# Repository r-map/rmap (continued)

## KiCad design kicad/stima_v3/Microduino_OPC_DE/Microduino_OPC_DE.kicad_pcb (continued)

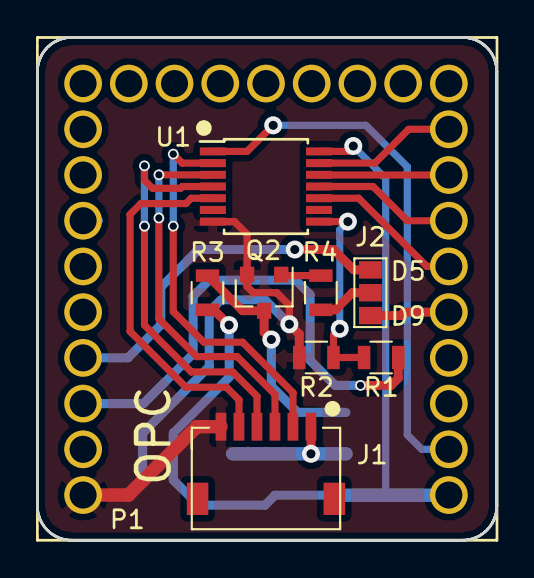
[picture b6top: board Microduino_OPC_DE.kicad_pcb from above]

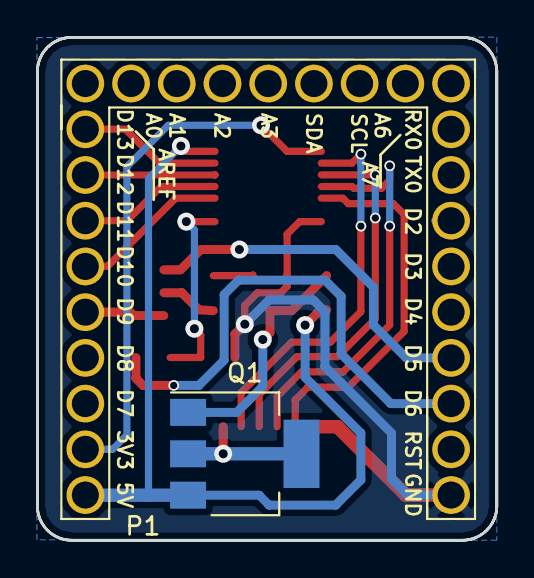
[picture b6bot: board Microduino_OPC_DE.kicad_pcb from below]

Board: 2 copper layers, 25.5 x 27.9 mm, 10 parts (2 on the bottom side), 19 nets.

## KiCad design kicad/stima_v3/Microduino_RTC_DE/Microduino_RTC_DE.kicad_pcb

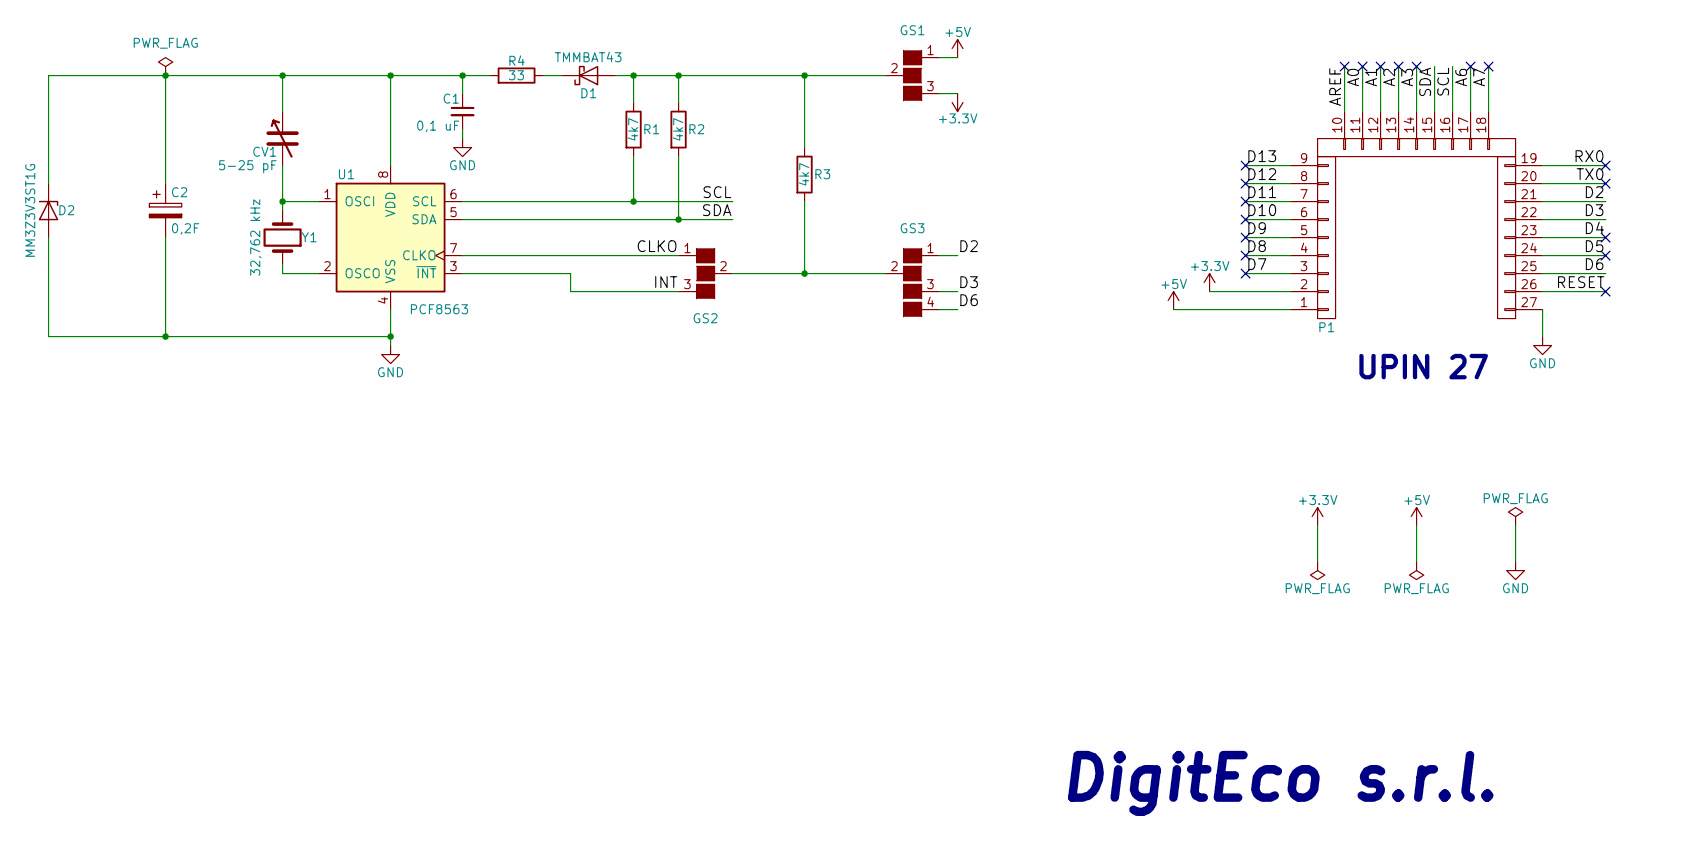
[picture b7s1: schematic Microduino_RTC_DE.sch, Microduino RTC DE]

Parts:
C1: 0,1 uF; C_0805
C2: 0,2F; Supercap
CV1: 5-25 pF; C_1206
D1: TMMBAT43; D_MiniMELF_Standard
D2: MM3Z3V3ST1G; D_SOD-323
GS1, GS2: GS3
GS3: GS4
P1: CONN_1x27; Upin_27
R1, R2, R3: 4k7; R_0805
R4: 33; R_0805
U1: PCF8563; SOIC-8_3.9x4.9mm_Pitch1.27mm
Y1: 32,762 kHz; Crystal_SMD_G8-2pin_3.2x1.5mm_HandSoldering

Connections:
+3V3: GS1.3 (G3), P1.2
+5V: GS1.1 (G1), P1.1
/A0: P1.11
/A1: P1.12
/A2: P1.13
/A3: P1.14
/A6: P1.17
/A7: P1.18
/AREF: P1.10
/CLKO: GS2.1 (G1), U1.7 (CLKO); also elsewhere on the board
/D2: GS3.1 (G1), P1.21
/D3: GS3.3 (G3), P1.22
/D4: P1.23
/D5: P1.24
/D6: GS3.4 (G4), P1.25
/D7: P1.3
/D8: P1.4
/D9: P1.5
/D10: P1.6
/D11: P1.7
/D12: P1.8
/D13: P1.9
/INT: GS2.3 (G3), U1.3 (~INT~); also elsewhere on the board
/RESET: P1.26
/RX0: P1.19
/SCL: P1.16, R1.2, U1.6 (SCL)
/SDA: P1.15, R2.2, U1.5 (SDA)
/TX0: P1.20
GND: C1.2, C2.2, D2.2 (A), P1.27, U1.4 (VSS)
unnamed: C1.1, C2.1, CV1.1, D2.1 (K), R4.2, U1.8 (VDD)
unnamed: CV1.2, U1.1 (OSCI), Y1.2
unnamed: D1.1 (K), R4.1
unnamed: D1.2 (A), GS1.2 (G2), R1.1, R2.1, R3.1
unnamed 33: GS2.2 (G2), GS3.2 (G2), R3.2; also elsewhere on the board
unnamed: U1.2 (OSCO), Y1.1

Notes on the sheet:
UPIN 27
DigitEco s.r.l.

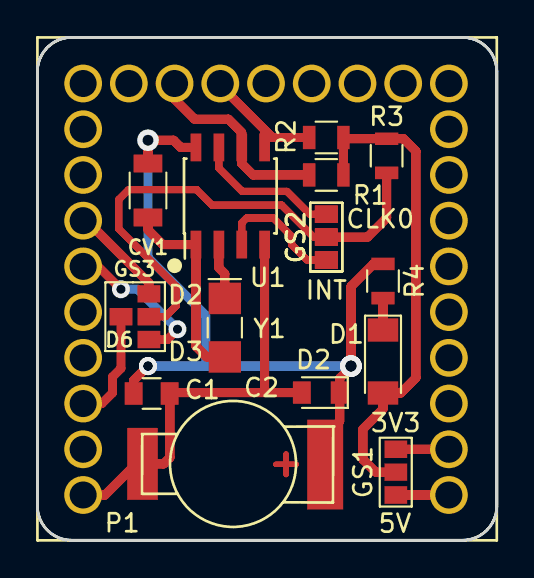
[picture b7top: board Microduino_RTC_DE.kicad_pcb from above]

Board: 2 copper layers, 25.5 x 27.9 mm, 16 parts (1 on the bottom side), 16 nets.

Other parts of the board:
GS2#2: GS3

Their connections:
/CLKO: GS2#2.1; also elsewhere on the board
/INT: GS2#2.3; also elsewhere on the board
unnamed 33: GS2#2.2; also elsewhere on the board

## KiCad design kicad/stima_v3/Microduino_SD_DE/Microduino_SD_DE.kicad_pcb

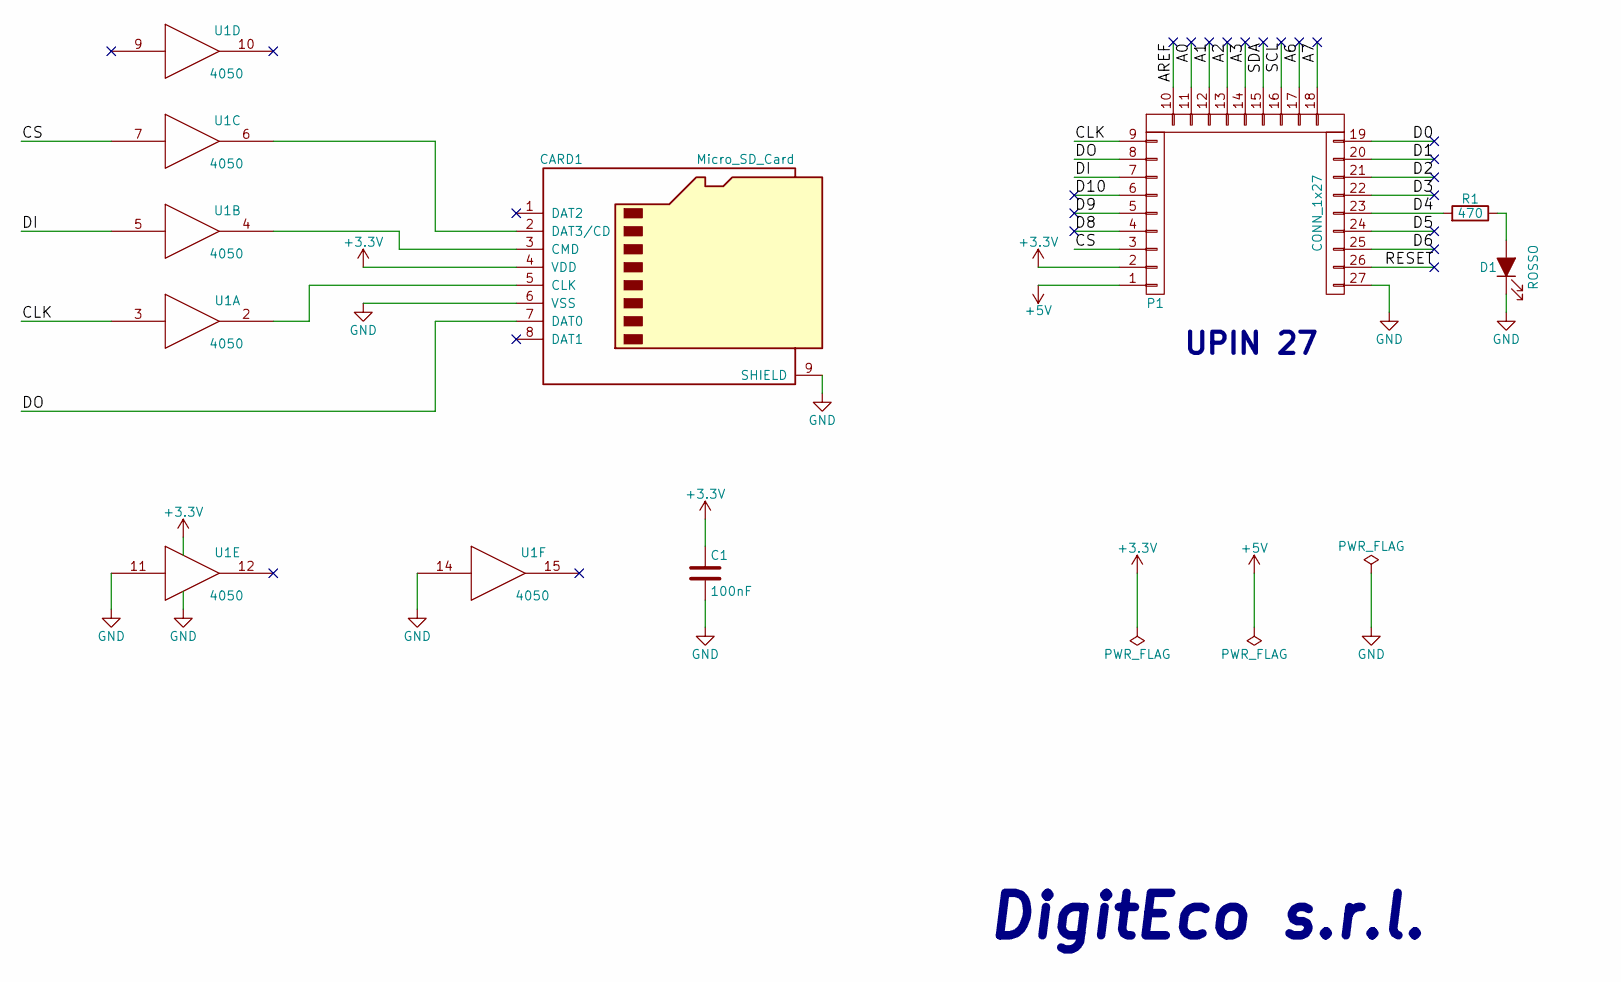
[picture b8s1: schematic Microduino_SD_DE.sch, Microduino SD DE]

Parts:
C1: 100nF; C_0805
CARD1: Micro_SD_Card; microSD_Card_Receptacle_Wuerth_693072010801
D1: ROSSO; LED_0805
P1: CONN_1x27; Upin_27
R1: 470; R_0805
U1: 4050; TSSOP-16_4.4x5mm_Pitch0.65mm

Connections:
+3V3: C1.1, CARD1.4 (VDD), P1.2, U1.1 (VCC)
+5V: P1.1
/A0: P1.11
/A1: P1.12
/A2: P1.13
/A3: P1.14
/A6: P1.17
/A7: P1.18
/AREF: P1.10
/CLK: P1.9, U1.3
/CS: P1.3, U1.7
/D0: P1.19
/D1: P1.20
/D2: P1.21
/D3: P1.22
/D4: P1.23, R1.2
/D5: P1.24
/D6: P1.25
/D8: P1.4
/D9: P1.5
/D10: P1.6
/DI: P1.7, U1.5
/DO: CARD1.7 (DAT0), P1.8
/RESET: P1.26
/SCL: P1.16
/SDA: P1.15
GND: C1.2, CARD1.6 (VSS), CARD1.9 (SHIELD), D1.1 (K), P1.27, U1.8 (VSS), U1.11, U1.14
unnamed: CARD1.2 (DAT3/CD), U1.6
unnamed: CARD1.3 (CMD), U1.4
unnamed: CARD1.5 (CLK), U1.2
unnamed: D1.2 (A), R1.1

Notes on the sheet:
UPIN 27
DigitEco s.r.l.

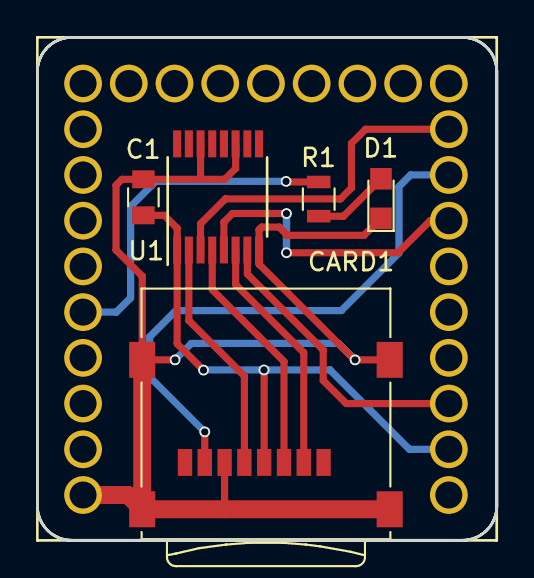
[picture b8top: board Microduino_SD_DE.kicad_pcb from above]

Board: 2 copper layers, 25.5 x 27.9 mm, 6 parts (1 on the bottom side), 11 nets.
